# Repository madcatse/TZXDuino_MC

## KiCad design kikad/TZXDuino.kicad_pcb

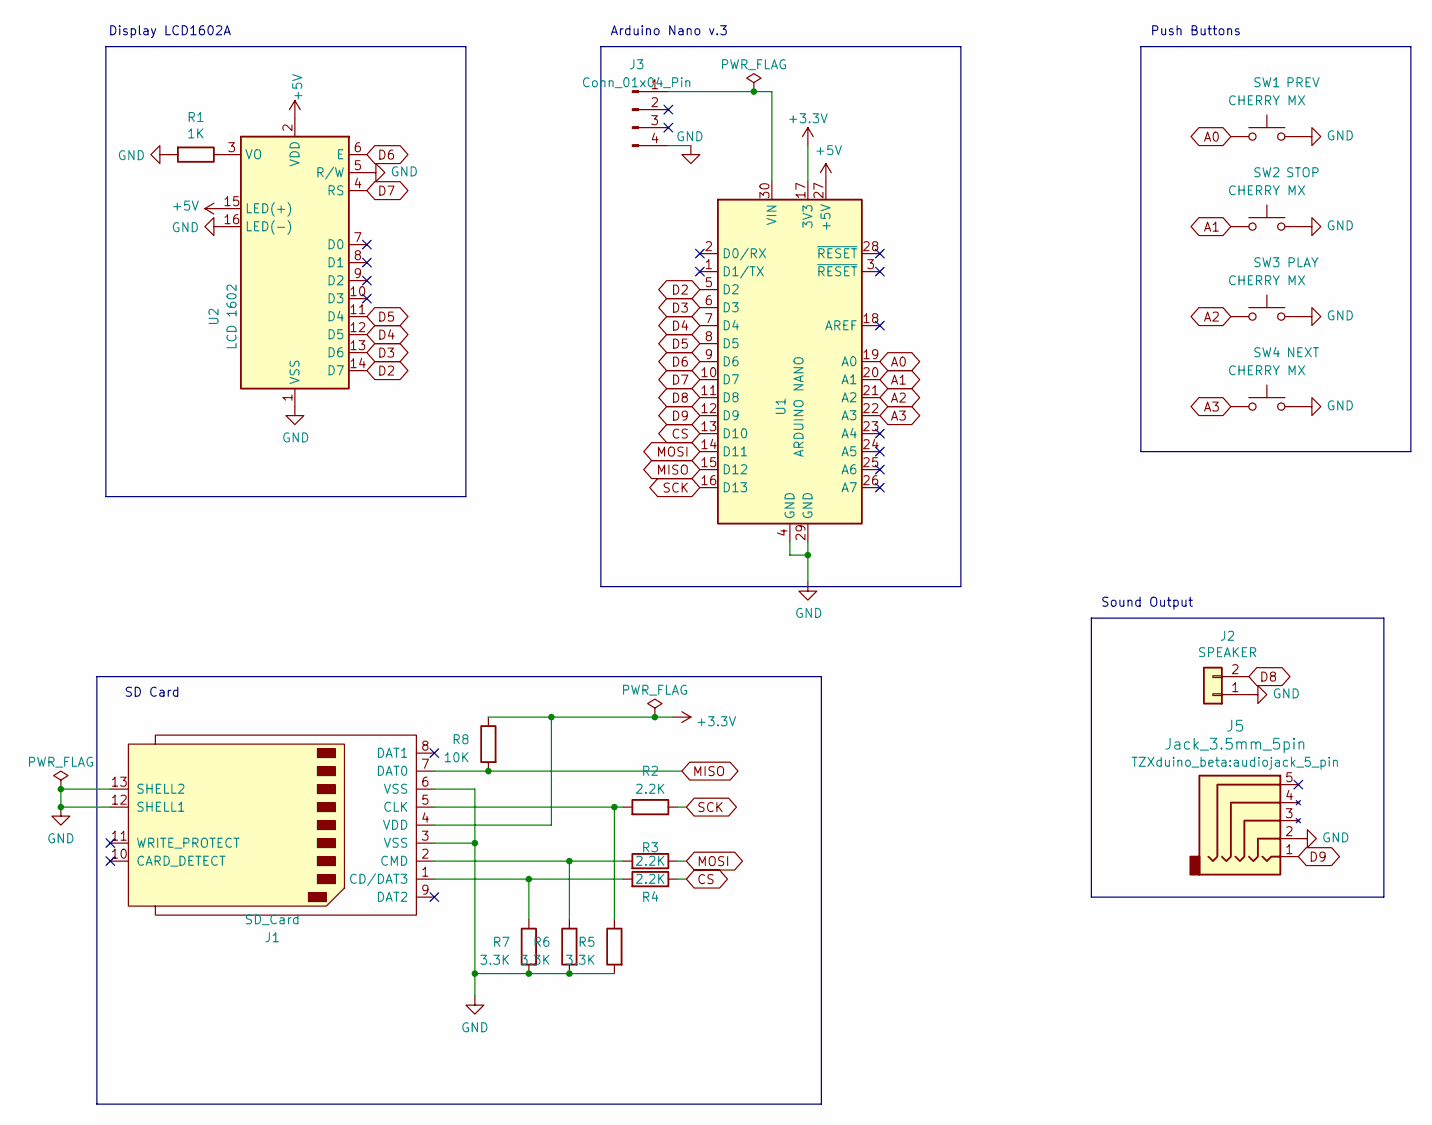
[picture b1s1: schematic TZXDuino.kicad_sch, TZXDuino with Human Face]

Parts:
J1: SD_Card; SDCARD_4UCONN
J2: SPEAKER; Speaker
J3: Conn_01x04_Pin; USB-C Power board
J5: Jack_3.5mm_5pin; audiojack_5_pin
R1: 1K; R_Axial_DIN0207_L6.3mm_D2.5mm_P10.16mm_Horizontal
R2, R3, R4: 2.2K; R_Axial_DIN0207_L6.3mm_D2.5mm_P10.16mm_Horizontal
R5, R6, R7: 3.3K; R_Axial_DIN0207_L6.3mm_D2.5mm_P10.16mm_Horizontal
R8: 10K; R_Axial_DIN0207_L6.3mm_D2.5mm_P10.16mm_Horizontal
SW1, SW2, SW3, SW4: CHERRY MX; SW_Cherry_MX_1.00u_PCB
U1: ARDUINO NANO; Arduino_Nano
U2: LCD 1602; LCD1602

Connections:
+3.3V: J1.4 (VDD), R8.1, U1.17 (3V3)
+5V: U1.27 (+5V), U2.2 (VDD), U2.15 (LED(+))
A0: SW1.1, U1.19 (A0)
A1: SW2.1, U1.20 (A1)
A2: SW3.1, U1.21 (A2)
A3: SW4.1, U1.22 (A3)
CS: R4.1, U1.13 (D10)
D2: U1.5 (D2), U2.14 (D7)
D3: U1.6 (D3), U2.13 (D6)
D4: U1.7 (D4), U2.12 (D5)
D5: U1.8 (D5), U2.11 (D4)
D6: U1.9 (D6), U2.6 (E)
D7: U1.10 (D7), U2.4 (RS)
D8: J2.2, U1.11 (D8)
D9: J5.1, U1.12 (D9)
GND: J1.3 (VSS), J1.6 (VSS), J1.12 (SHELL1), J1.13 (SHELL2), J2.1, J3.4, J5.2, R1.2, R5.2, R6.2, R7.2, SW1.2, SW2.2, SW3.2, SW4.2, U1.4 (GND), U1.29 (GND), U2.1 (VSS), U2.5 (R/W), U2.16 (LED(-))
MISO: J1.7 (DAT0), R8.2, U1.15 (D12)
MOSI: R3.1, U1.14 (D11)
unnamed: J1.1 (CD/DAT3), R4.2, R7.1
unnamed: J1.5 (CLK), R2.2, R5.1
unnamed: J1.2 (CMD), R3.2, R6.1
unnamed: J3.1, U1.30 (VIN)
unnamed: R1.1, U2.3 (VO)
SCK: R2.1, U1.16 (D13)

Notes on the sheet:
Push Buttons
Sound Output
Display LCD1602A
Arduino Nano v.3
SD Card

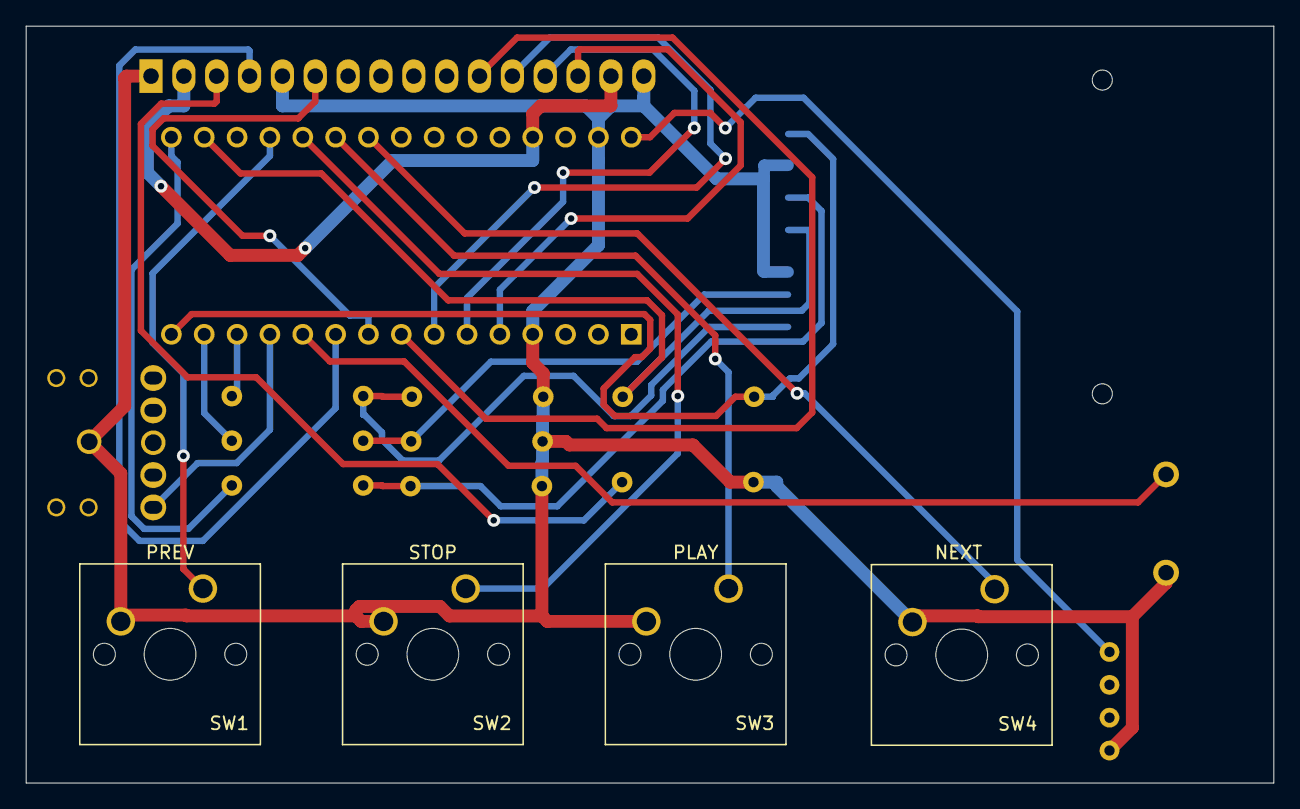
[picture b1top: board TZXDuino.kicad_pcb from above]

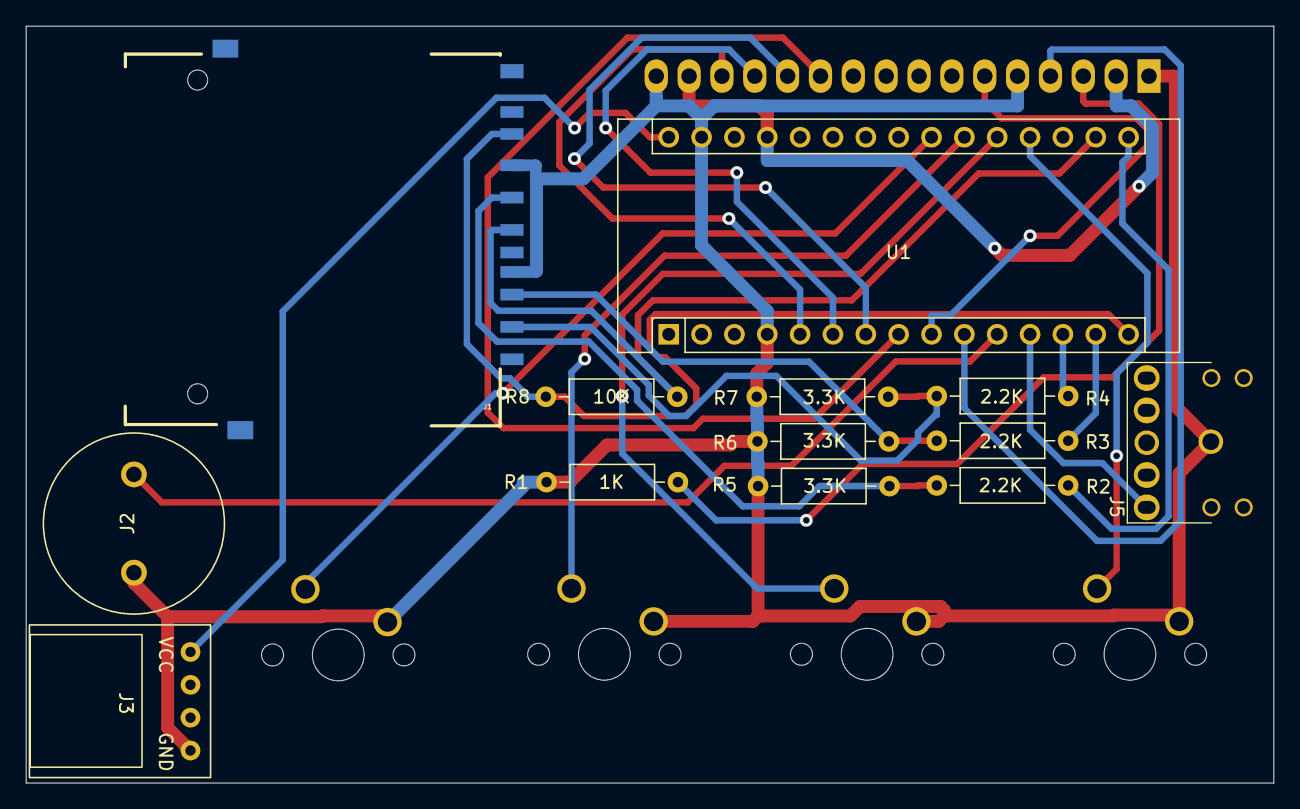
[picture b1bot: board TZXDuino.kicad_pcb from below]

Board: 2 copper layers, 96.5 x 58.5 mm, 18 parts (13 on the bottom side), 24 nets.

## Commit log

2024-02-12 Kicad sources
2024-02-12 Fixing
2024-03-20 Gerbers
